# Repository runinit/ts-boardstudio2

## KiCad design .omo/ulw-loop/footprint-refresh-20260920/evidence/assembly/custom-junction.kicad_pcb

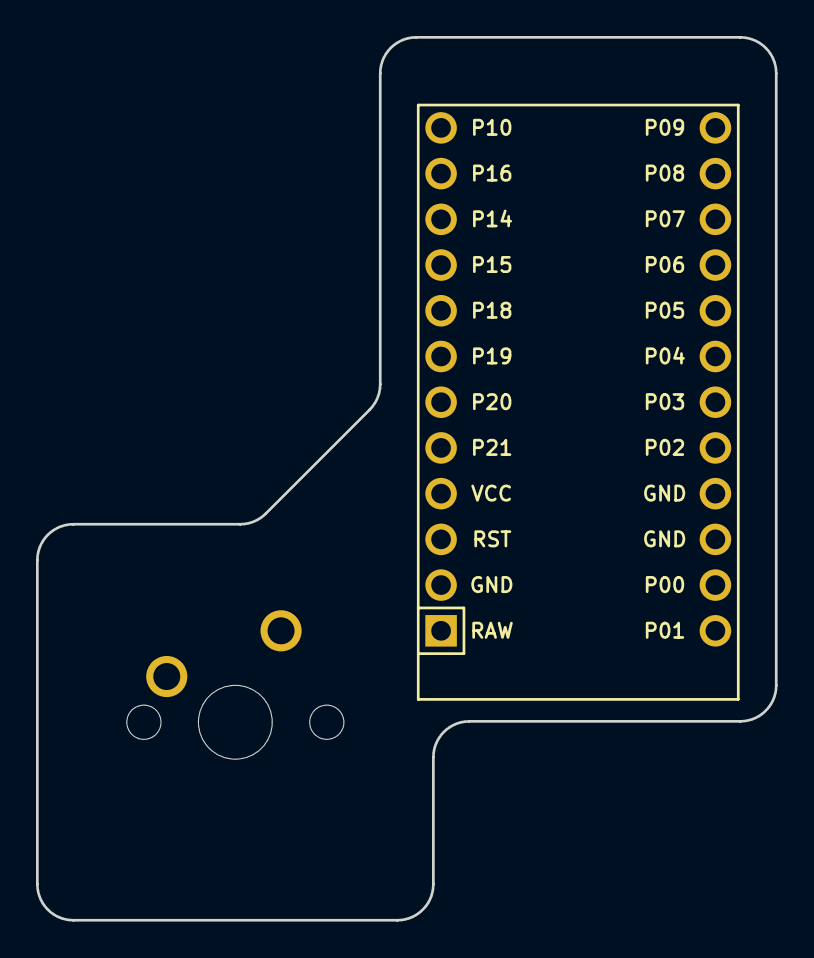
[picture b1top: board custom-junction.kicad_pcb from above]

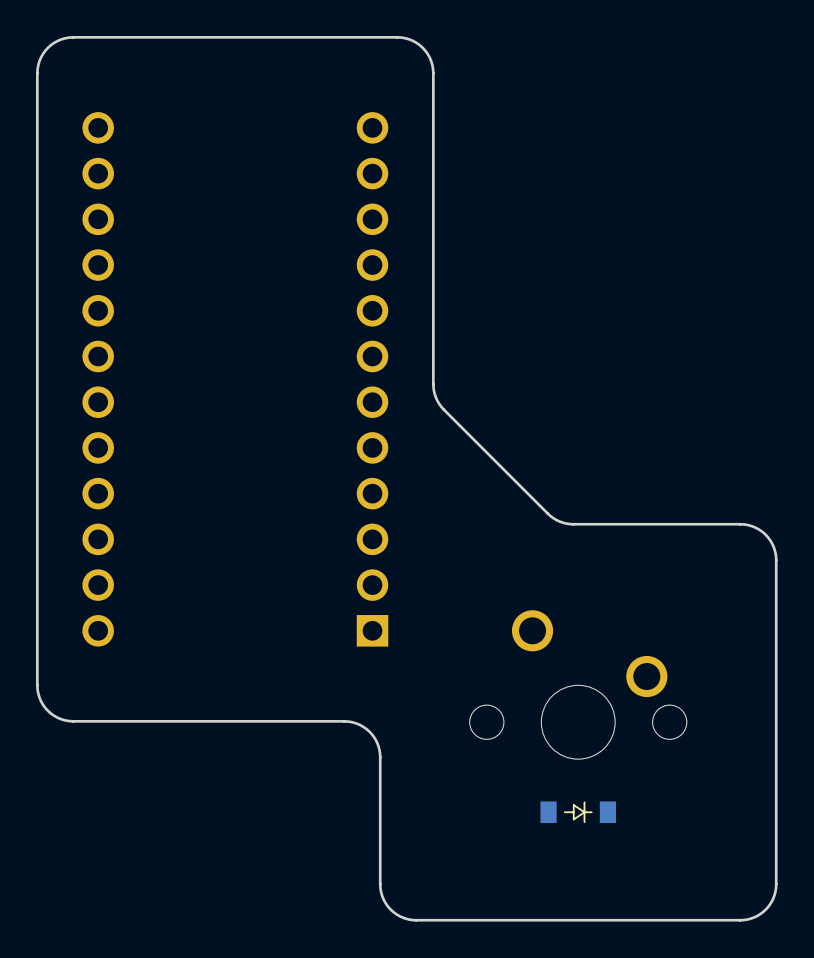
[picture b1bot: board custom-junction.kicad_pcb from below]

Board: 2 copper layers, 41.0 x 49.0 mm, 3 parts (2 on the bottom side), 4 nets, no tracks yet.

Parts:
X16970d43: ProMicro
Xec10466e: diode_tht_sod123
Xf89d51b7: switch_mx

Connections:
C1: X16970d43.14, Xf89d51b7.1
CUSTOM: X16970d43.17, Xec10466e.2, Xf89d51b7.2
GND: X16970d43.2, X16970d43.15, X16970d43.16
R1: X16970d43.13, Xec10466e.1

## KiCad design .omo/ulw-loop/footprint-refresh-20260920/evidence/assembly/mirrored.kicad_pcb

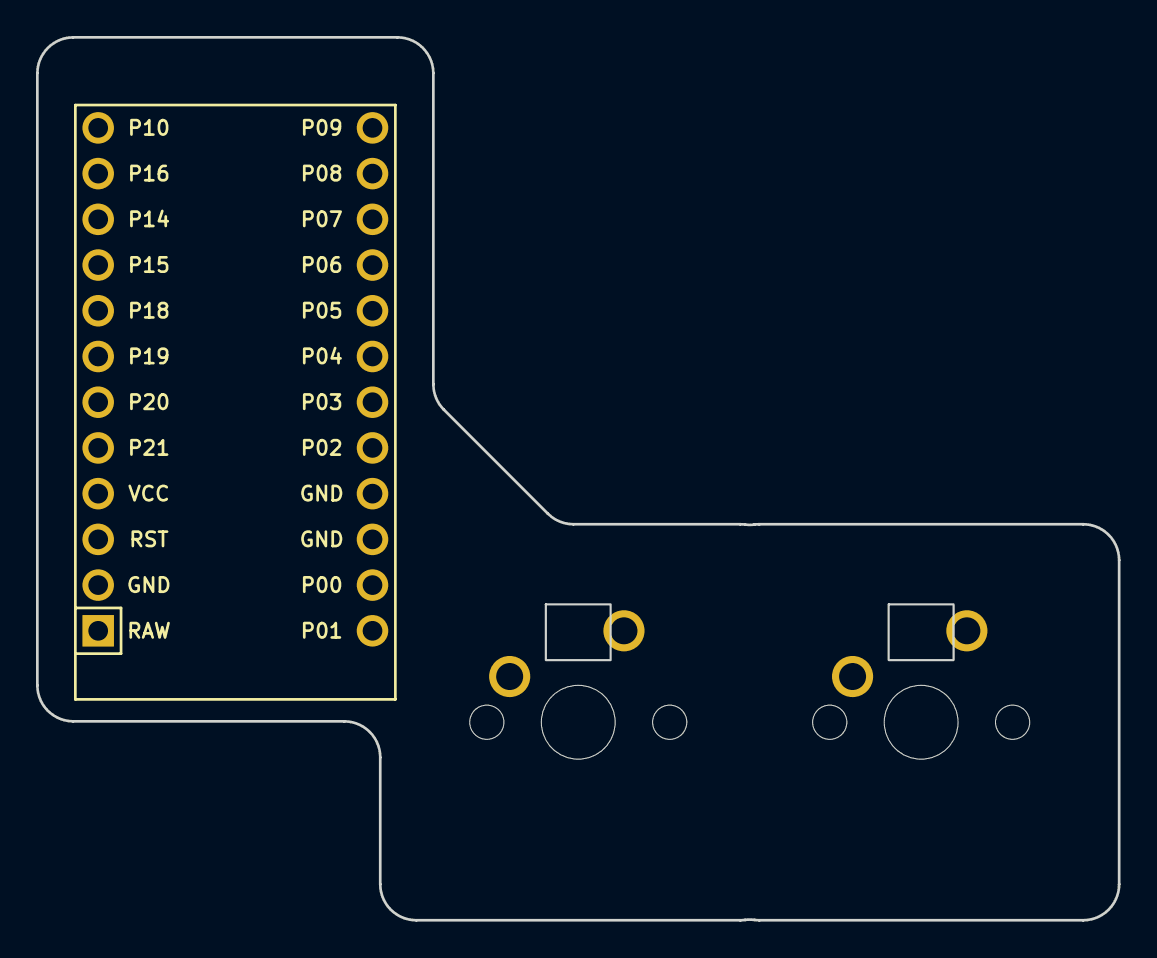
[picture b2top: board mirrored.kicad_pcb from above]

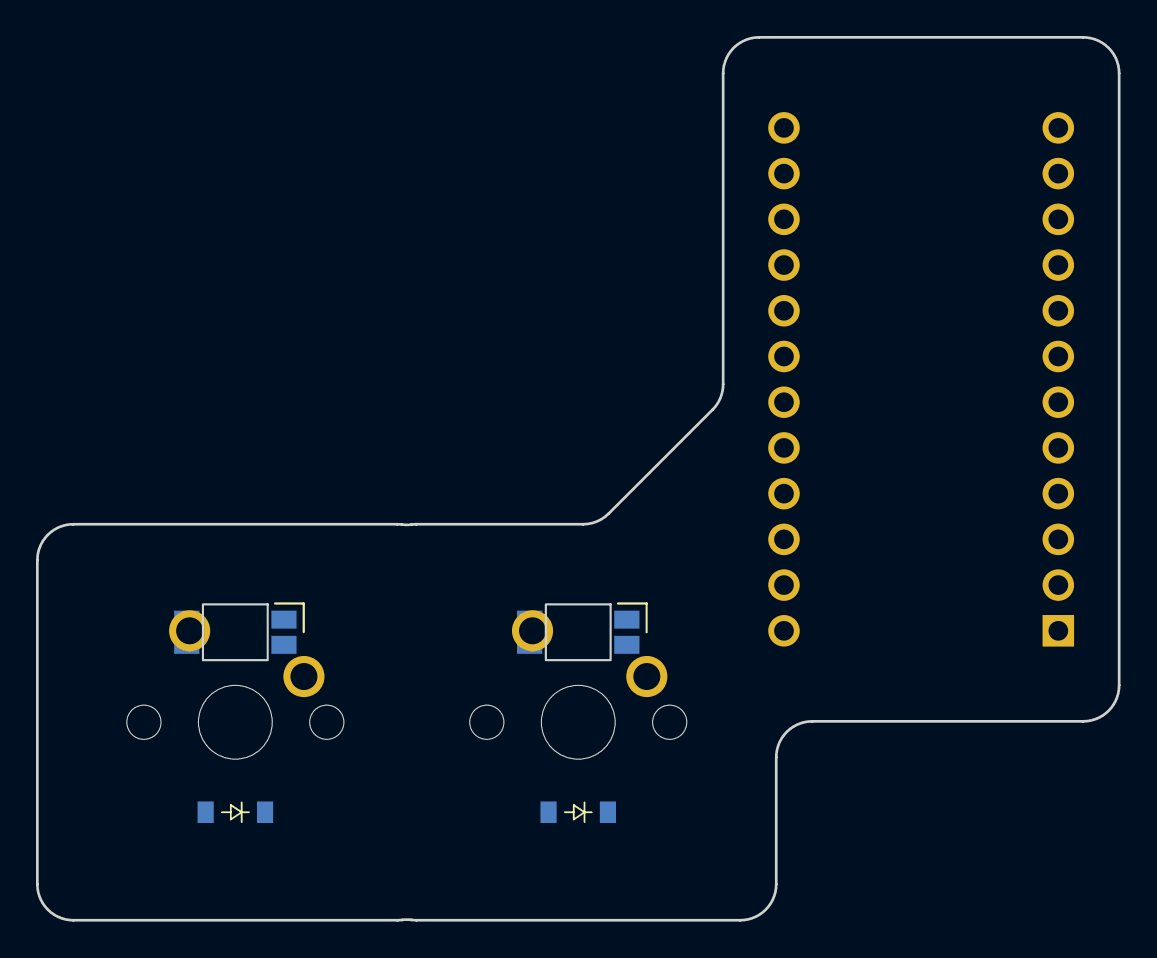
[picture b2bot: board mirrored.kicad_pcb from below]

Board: 2 copper layers, 60.1 x 49.1 mm, 7 parts (6 on the bottom side), 9 nets, no tracks yet.

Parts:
X8ee9b9a1, X803e5b04: switch_mx
X45e22880: diode_tht_sod123
X8949c7ae, X831473df: led_SK6812mini-e (per-keysingle-side)
Xa41ada51: diode_tht_sod123
Xe41c6407: ProMicro

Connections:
GND: X8949c7ae.3, X831473df.3, Xe41c6407.2, Xe41c6407.15, Xe41c6407.16
VCC: X8949c7ae.1, X831473df.1, Xe41c6407.4
right_C1: X8ee9b9a1.1, Xe41c6407.14
right_C2: X803e5b04.1, Xe41c6407.13
right_LED_1: X8949c7ae.2, X831473df.4
right_LED_DATA: X8949c7ae.4, Xe41c6407.18
right_R1: X45e22880.1, Xa41ada51.1, Xe41c6407.17
right_fingers_c1_r1_switch: X8ee9b9a1.2, X45e22880.2
right_fingers_c2_r1_switch: X803e5b04.2, Xa41ada51.2

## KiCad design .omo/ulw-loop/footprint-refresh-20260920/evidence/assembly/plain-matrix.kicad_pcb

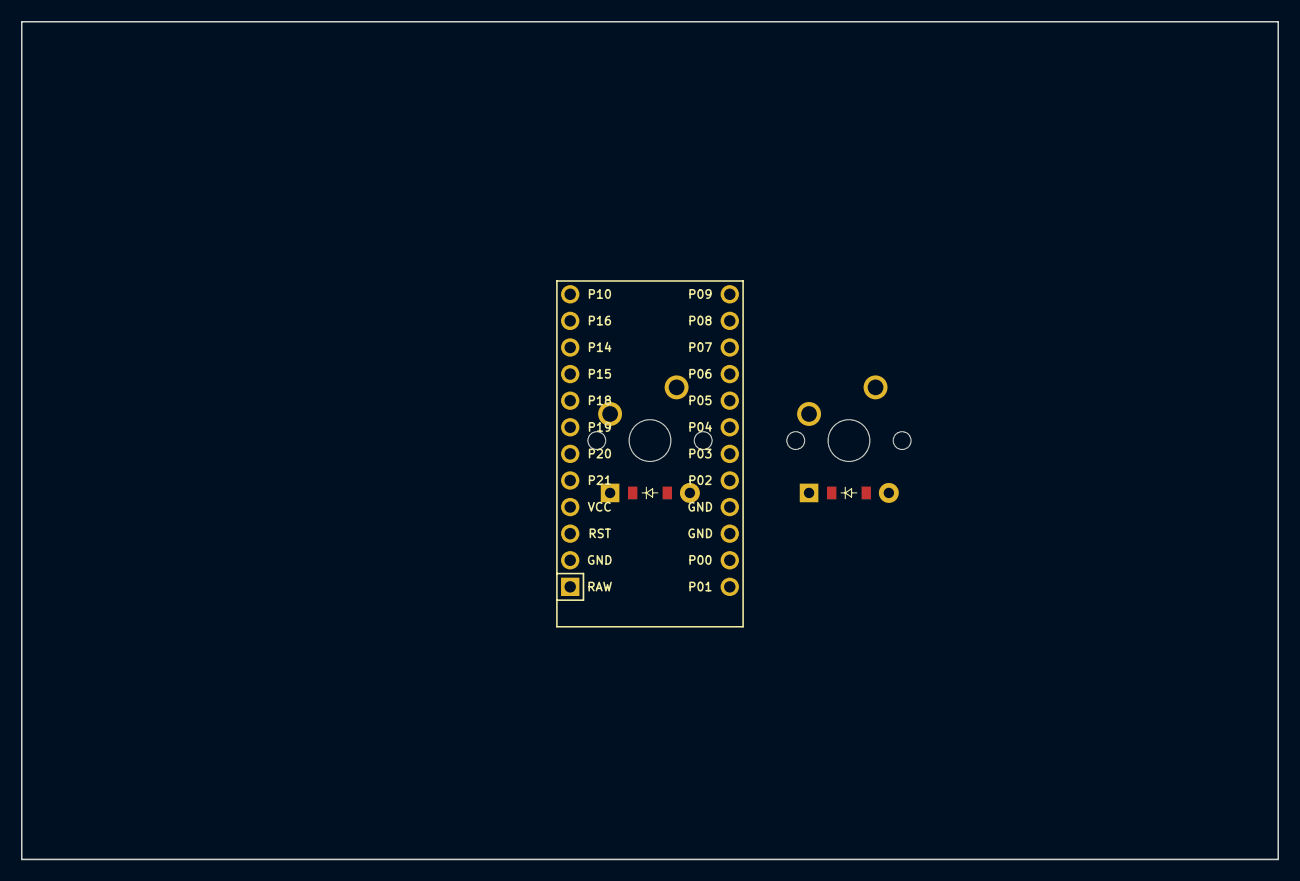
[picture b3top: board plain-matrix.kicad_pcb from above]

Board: 2 copper layers, 120.0 x 80.0 mm, 5 parts (0 on the bottom side), 6 nets, no tracks yet.

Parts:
X8d4cc759: ComboDiode
X9c733b1c: ProMicro
X876ba2fe: MX
Xb2d7db84: ComboDiode
Xf89d51b7: MX

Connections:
GND: X9c733b1c.2, X9c733b1c.15, X9c733b1c.16
fingers_c1: X9c733b1c.14, Xf89d51b7.1
fingers_c1_r1_switch: X8d4cc759.2, Xf89d51b7.2
fingers_c2: X9c733b1c.17, X876ba2fe.1
fingers_c2_r1_switch: X876ba2fe.2, Xb2d7db84.2
fingers_r1: X8d4cc759.1, X9c733b1c.13, Xb2d7db84.1
